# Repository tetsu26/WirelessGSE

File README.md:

# GSE Ver.2 の解説
東北大学FROM THE EARTH用のGSE制御システムVer.2の解説です．    
質問等は tetsushi_m[at]outlook.jp まで．

# はじめに
FTEのGSEを無線化した経緯について書いておきます．

時は遡ること2017年，この年の能代で突然，点火点と射点の位置が20mくらい伸びたため，今まで使っていたGSEのケーブルの長さが足りなくなってしまったのです．そこで燃焼班の皆様はLANケーブルを調達し，なんか頑張ってどうにかなった（詳しくはよく知らん）のですが，そのときの燃焼班のケーブル半田付けなどがまぁそれはそれは残念だったので，電子班でどうにかしようということになりました．んで，当時流行だった無線GSEに憧れた7期はどうせならFTEのGSEも無線化しちまおうとなったわけです．自然な流れですね．そして当時電子班班長だった私は電子班の誰かに無線GSE開発を押しつけようと声をかけ続けた訳ですが，何かと理由をつけて全員に断られてしまったので仕方なく自分でやることにしたわけです．

そうして無線GSEを作ることになってしまった私ですが，当初はロケットの電装に比べれば，スイッチの状態を送信するだけなんで簡単だろうと高をくくっていた訳です．まぁ"スイッチの状態を送るだけなら"実際簡単な訳ですが．実際作ってみるといろいろな障壁がありました．
* 送信レートの問題
  
  IM920で使ってる920MHz帯は送信時間の制限が厳しくて，データを連続送信できないため，5Hz位でしかスイッチの状態を反映できない．
* IM920 の通信距離
  
  7km飛ぶとかいっときながら見通しでも300m位しか通信できない．ちょっと怖い．
* 打ち上げシーケンス中に通信途切れた時の対処
  
  ダンプするしかない．悲しい．
* 卍伊豆大島卍
  
  活火山なだけあって何かが島から出ている．無線が飛ばない．見通しで100mがやっと．
* 責任
  
  無線GSEがしくじるとロケットが飛ばない訳でみんなの努力が報われない．打ち上げ前は気が気じゃない．
  
そのたもろもろ．思ったより大変だった．

そんなこんなで無線GSEを作っていると思うわけです．点火点と射点，ケーブルでつなげばよくね？　俗に言う原点回帰って奴です．有線なら通信の安定性とか考えなくていいし，ケーブルの断線だけ気をつけていればいいよね．そこで電子班何人かで有線GSEを総点検し，やばそうな半田付けは直し，ケーブルも完璧に作り直しました．

つまり，このくそ長いはじめにで何が言いたいかというと，**「無線使うな有線を使え」** ということです．きっとこれを読んでいるあなたは不幸にも無線GSEを押しつけられてしまったしがない電子班員でしょう．ご愁傷さま．燃焼班員にあったら是非伝えてください． **「無線使うな有線を使え」** と．あいつらはこの無線GSEのやばさを知りません．健闘を祈ります．

# よく燃焼班に聞かれること・注意すべきこと
* 無線のチャンネルは？  
  プログラムコードからは変更できない．IM920の設定から変更する．ググれば出てくるし，[この辺のサイト](https://www.interplan.co.jp/solution/wireless/im920/im920.php)を参考にすべし．

* 安全対策は？  
  万が一Fill中に通信が途絶えてもFillが止まるように，Fillには時間制限がかかっている．時間制限はロケット側のGSEのプログラムを書き換えることで変更できる．デフォルトでは60秒以上Fillが続くと強制的に30秒ダンプする．  
  同様に，Oxyも60秒以上入らないようになっている．このときはダンプせず，システムを再起動する．

# 使っている主な部品  
* マイコン    MBED LPC1768  
まぁいつもの．ピンがいっぱいあるから．
* 3端子dcdc   BP5293-50   http://akizukidenshi.com/catalog/g/gM-11188/  
3端子レギュレーターは効率悪いし，村田のdcdcコンバータは半田付けが難しすぎるので．  
ざっと計算した感じ，1Aもあれば，IM920含めて余裕で足りる．
* リレー    946H-1C-5D  http://akizukidenshi.com/catalog/g/gP-07342/  
mbedのdigital out は40mAまでしか出せないので，リレーは動かせなさそうだった．  
5Vのリレーをトランジスタでスイッチングするのがいいと思った．   
* 無線モジュール    IM920  
協賛でもらったやつ．正直無線GSEには向いてない．

# プログラムコード
\SourceCode にあります．mbedオンラインコンパイラにコピペして使ってください．
ロケット側と点火点側でソースコードが分かれてるんで気をつけてください．

## コード解説_点火点側
ソースコードはc++(ほぼC)で書いてあります．一応頭から説明しておきます．

```cpp
#include<mbed.h>
#include<IM920.h>
#include<cstring>
```
ライブラリのインポートです（それはそう）．

```cpp
#define IM920_TX p13
#define IM920_RX p14
#define IM920_BUSY p11
#define IM920_RESET p12
#define IM920_SERIAL_BANDRATE 19200//im920の通信レート
```
IM920関係のピン設定ですね．

```cpp
DigitalOut myled(LED1);
DigitalOut myled2(LED2);
DigitalOut myled3(LED3);
DigitalOut myled4(LED4);
DigitalOut led_fill(p16);
DigitalOut led_dump(p18);
DigitalOut led_oxy(p20);
DigitalOut led_fire(p21);
DigitalOut led_1(p24);
DigitalOut led_2(p23);
PwmOut buzzer(p26);

DigitalIn fill(p15);
DigitalIn dump(p17);
DigitalIn oxy(p19);
DigitalIn fire(p22);

IM920 im920(p13, p14, p11, p12,19200);//無線通信用のserialクラス
Serial pc(USBTX, USBRX);
```
そのたもろもろのピン設定です．基板自作したときは適宜変えてください．

```cpp
// グローバルな奴ら
char send_data[8];    //送信するデータを格納する変数
char recv_data[8];    //受信すry)
int cb_count = 0;     //割り込み回数を数えるやつ
int i = 0;            //一秒間隔で赤いLEDを点滅させるのに使う
```
グローバル変数です．

```cpp
int fire_buzzer(int i)
{
    if(i == 1)
    {
        buzzer.period(1.0/440.0);  //多分"ラ"
        buzzer.write(0.5f);
        wait(0.5f);
        buzzer.write(0.0f);
    }
    
    return 0;
}
```
これは fire をオンにしたときにブザーから音を出すための関数です．音程が気に入らない人は変えてください．

### callback() 関数

```cpp
void callback () {  //受信時の割り込み関数（受信したときに送信するコード）
    int i;

    cb_count++; //割り込みの回数を数える変数
    
    i = im920.recv(recv_data, 8);
    recv_data[i] = 0;
    pc.printf("recv: '%s' (%d)\r\n", recv_data, i);
    
    if (recv_data[0] == '5' || recv_data[7] == '5')     //きちんとデータを受け取れたか確認
    {
        led_fill = recv_data[1] - '0';           
        led_dump = recv_data[2] - '0';
        led_oxy = recv_data[3] - '0';
        led_fire = recv_data[4] - '0';
        fire_buzzer(led_fire);
    }
    //8文字1セットで送ることにする
    send_data[0] = '5';   //データ始まりの合図
    send_data[1] = '0'+(fill.read()^ 1);      //プルアップしてるからHiとLoを反転
    send_data[2] = '0'+(dump.read()^ 1);
    send_data[3] = '0'+(oxy.read()^ 1);
    send_data[4] = '0'+(fire.read()^ 1);
    // 5~6はとりあえず未使用
    send_data[5] = '0';
    send_data[6] = '0';
    send_data[7] = '5';   //データ終わりの合図
        
    im920.sendData(send_data,8);    //8文字送りますよーってやつ
    //pc.printf("send:%s\r\n cb_count:%d\r\n",send_data,cb_count);

}
```
これはim920が受信したときに実行される予定の関数です．グローバル関数にiがあるのにローカルでもiを宣言して使うくそコードになってますね，今気づきました．ここからわかりにくいと思うので詳しく書いておきます．
```cpp
i = im920.recv(recv_data, 8);
recv_data[i] = 0;
pc.printf("recv: '%s' (%d)\r\n", recv_data, i);
```
この辺はおまじないです．書いておいてください．
```cpp
if (recv_data[0] == '5' || recv_data[7] == '5')     //きちんとデータを受け取れたか確認
    {
        led_fill = recv_data[1] - '0';           
        led_dump = recv_data[2] - '0';
        led_oxy = recv_data[3] - '0';
        led_fire = recv_data[4] - '0';
        fire_buzzer(led_fire);
    }
```
これは効果あるかは謎ですが，受信したデータの整合性を確認しているつもりです．受信データ（8桁）の最初と最後の数字は`5`なのでそれだけ確認しています．

その後の`led_fill = recv_data[1] - '0';`ですが，これは受信した8桁の2文字目がfillの状態を示しているのでそれをスイッチについたLEDに反映しています．受信したデータは`recv_data`に格納されているのですが，ASCIIコードなので`0`のASCIIコードを引くことで元の送信した数字に戻しています．ほかも同じです．
```cpp
 //8文字1セットで送ることにする
    send_data[0] = '5';   //データ始まりの合図
    send_data[1] = '0'+(fill.read()^ 1);      //プルアップしてるからHiとLoを反転
    send_data[2] = '0'+(dump.read()^ 1);
    send_data[3] = '0'+(oxy.read()^ 1);
    send_data[4] = '0'+(fire.read()^ 1);
    // 5~6はとりあえず未使用
    send_data[5] = '0';
    send_data[6] = '0';
    send_data[7] = '5';   //データ終わりの合図
```
この辺はスイッチの状態を読み取って送信するデータを作っています．`send_data`配列の５と６は将来のために未使用です．送る文字数を８文字にしたのはなんとなくきりがいいからです．
```cpp
im920.sendData(send_data,8);    //8文字送りますよーってやつ
```
そしてここで上で作った文字列を送信しています．

### callback2() 関数
```cpp
void callback2()    //受信割り込みの回数を数える関数
{
    
    if(cb_count == 0)
    {
        pc.printf("yabame\r\n");
        NVIC_SystemReset();         //一秒間に一回も通信しなかったらリセットする
        
    }
    else
    {
        cb_count = 0;
        if(i == 0)
        {
            led_2 = 1;
            i++;
        }else{
            led_2 = 0;
            i = 0;
        }

    }
}
```
これは接続が切れたときの対処です．コードをざっくり見てもらうと気づくと思うのですが，このコードには「受信したら割り込み処理で送信する」機能しかないので，一度接続が切れる（というかデータのやりとりが途絶える）と復帰できなくなる問題があります．なので`callback2()`関数を1秒ごとに起動してもしその前1秒間に一度も通信していなかったらこのmbedをリセットして`main()`関数をもう一度頭から実行します．`NVIC_SystemReset()`ってのはmbedのリセットボタンを押した状態をコードから作れる魔法の言葉です．

### main()関数
```cpp
int main()
{
    //各スイッチをプルアップする
    fill.mode(PullUp);
    dump.mode(PullUp);
    oxy.mode(PullUp);
    fire.mode(PullUp);          

    im920.init();
    //Im920受信の割り込みを設定
    im920.attach(callback);
    pc.baud(115200);
    pc.printf("Wireless GSE controll system started!!\r\n");
    
    Ticker timeout;
    timeout.attach(&callback2,1);
    
    myled = 1;  //設定完了の合図
    led_1 = 1; 
    im920.poll();
    im920.sendData(send_data,8);    
    
    while(1){   
        im920.poll();//双方向送受信に必要らしい
       // wait_ms(1);  //意味なさそうだけどあると安定する
        
    }
    
}
```
ここは特に説明することもない気がします．セットアップの時に1度データを送信します．

## コード解説_ロケット側
同じように解説書いておきます．
```cpp
#include<mbed.h>
#include<IM920.h>

#define IM920_TX p13
#define IM920_RX p14
#define IM920_BUSY p11
#define IM920_RESET p12
#define IM920_SERIAL_BANDRATE 19200//im920の通信レート

//LED&SWITCHたち      
DigitalOut myled(LED1);
DigitalOut myled2(LED2);
DigitalOut myled3(LED3);
DigitalOut myled4(LED4);
DigitalOut fill(p21);
DigitalOut dump(p22);
DigitalOut oxy(p23);
DigitalOut fire(p24);

IM920 im920(p13, p14, p11, p12,19200);//無線通信用のserialクラス
Serial pc(USBTX, USBRX);
```
まぁこの辺は説明するまでもないでしょ．
```cpp
char send_data[8];    //送信するデータを格納する変数
char recv_data[8];    //受信すry)
int fill_count = 0;     //fillの割り込みの回数を数えるやつ
int oxy_count = 0;     //oxyの割り込みの回数を数えるやつ
```
グローバル変数の定義．

### callback()関数
```cpp
void callback () {
    int i;
    int fire_count = 0;
    
    i = im920.recv(recv_data, 8);
    recv_data[i] = 0;
    printf("recv: '%s' (%d)\r\n", recv_data, i);
    
    if (recv_data[0] == '5' || recv_data[7] == '5')     //きちんとデータを受け取れたか確認
    {
        fill = recv_data[1] - '0';           
        dump = recv_data[2] - '0';
        oxy = recv_data[3] - '0';
        fire_count = recv_data[4] - '0';
        
        if(fire_count == 1 && oxy == 1){
            fire = 1;
        }else{
            fire = 0;
        }
        
    }
    /*
    for(int i = 0; i < 8; i++)
    {
        send_data[i] = recv_data[i];
    }
    */
    im920.sendData(recv_data,8);
    //printf("send!!:%s\r\n",recv_data);
}
```
点火点側の`callback`関数とほとんど同じです．ただ，`oxy`が入ってないと`fire`がオンにならないようにしてあります．

### fillcount()関数
```cpp
void fillcount()    //受信割り込みの回数を数える関数
{
    if(fill == 1)
    {
        fill_count += 1;
    }else{
        fill_count = 0;
    }
    
    if(oxy == 1)
    {
        oxy_count += 1;
    }else{
        oxy_count = 0;
    }
    
    printf("fill_count: %d\r\n",fill_count);
    printf("oxy_count: %d\r\n",oxy_count);
    if(fill_count >= 60)
    {
        fill = 0;
        dump = 1;
        printf("recovery mode!!! Dump 30second\r\n");
        wait(30);
        printf("reboot!!");
        NVIC_SystemReset(); 
        
    }
    if(oxy_count >= 60)
    {
        oxy = 0;
        printf("recovery mode!!!\r\n");
        printf("reboot!!");
        NVIC_SystemReset(); 
    }
    
}
```
この関数を1秒に一回割り込みさせることで，`fill`がオンになってる秒数などを数えています．
```cpp 
if(fill_count >= 60)
```
の60をいじるとFill時間に制限をかけられます．60の時は一分以上はFillできないという具合です．

### main()関数
```cpp
int main()
{
    
    pc.baud(115200);
    pc.printf("*** IM920\r\n");
    
    /* 受信側との接続を確立する */
    
    im920.init();

    im920.attach(callback);
    myled = 1;          //設定完了の合図
    
    Ticker fill_limit;
    fill_limit.attach(&fillcount,1);
    
    im920.poll();

    while(1){
       im920.poll();
       //wait_ms(1);
    }
    
}
```
特にいうことはないです．
```cpp
    Ticker fill_limit;
    fill_limit.attach(&fillcount,1);
```
でfillcount関数に1秒おきの割り込みを設定しています．

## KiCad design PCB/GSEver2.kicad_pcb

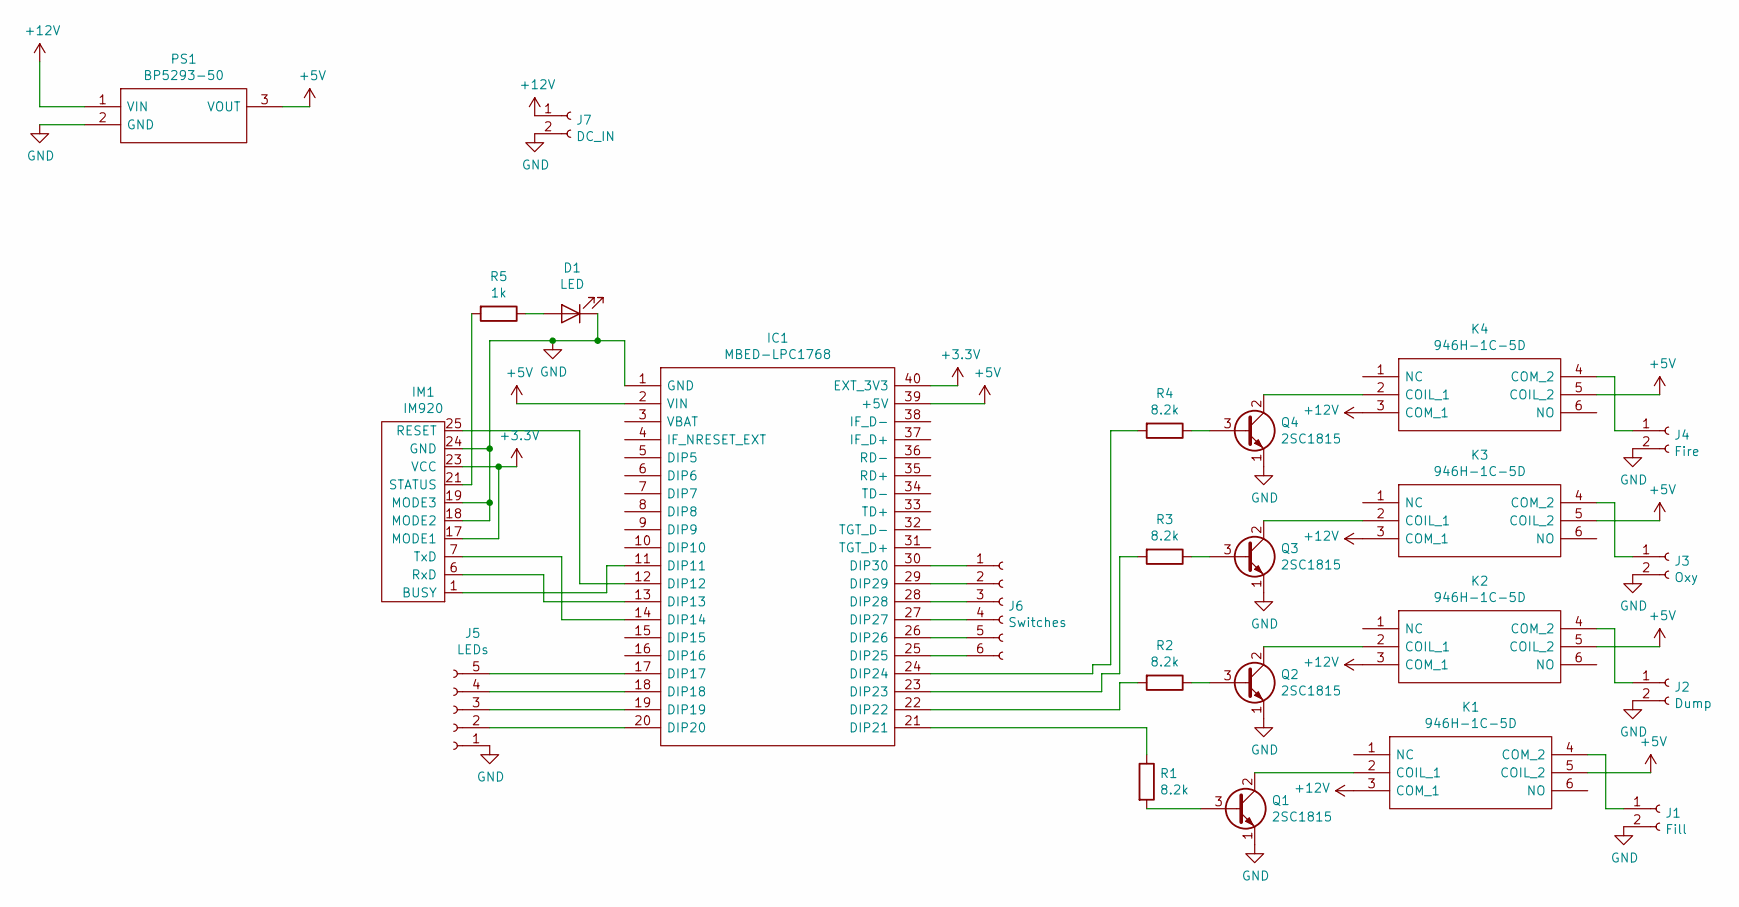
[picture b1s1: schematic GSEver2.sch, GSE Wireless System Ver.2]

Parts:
D1: LED; LED_D3.0mm
IC1: MBED-LPC1768; DIPS2286W63P254L5370H300Q40N; Manufacturer_Part_Number MBED-LPC1768
IM1: IM920
J1: Fill; JST_XH_B02B-XH-A_02x2.50mm_Straight
J2: Dump; JST_XH_B02B-XH-A_02x2.50mm_Straight
J3: Oxy; JST_XH_B02B-XH-A_02x2.50mm_Straight
J4: Fire; JST_XH_B02B-XH-A_02x2.50mm_Straight
J5: LEDs; JST_XH_B05B-XH-A_05x2.50mm_Straight
J6: Switches; JST_XH_B06B-XH-A_06x2.50mm_Straight
J7: DC_IN; JST_XH_B02B-XH-A_02x2.50mm_Straight
K1, K2, K3, K4: 946H-1C-5D; 946H1C5D; Manufacturer_Part_Number 946H-1C-5D
PS1: BP5293-50; TO254P570X1690X1800-3P; Manufacturer_Part_Number BP5293-50
Q1, Q2, Q3, Q4: 2SC1815; TO-92_Inline
R1, R2, R3, R4: 8.2k; R_Axial_DIN0207_L6.3mm_D2.5mm_P10.16mm_Horizontal
R5: 1k; R_Axial_DIN0207_L6.3mm_D2.5mm_P10.16mm_Horizontal

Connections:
+3V3: IC1.40 (EXT_3V3), IM1.17 (MODE1), IM1.23 (VCC); also elsewhere on the board
+5V: IC1.2 (VIN), IC1.39 (+5V), K1.5 (COIL_2), K2.5 (COIL_2), K3.5 (COIL_2), K4.5 (COIL_2), PS1.3 (VOUT); also elsewhere on the board
+12V: J7.1, K1.3 (COM_1), K2.3 (COM_1), K3.3 (COM_1), K4.3 (COM_1), PS1.1 (VIN)
GND: D1.1 (K), IC1.1 (GND), IM1.18 (MODE2), IM1.19 (MODE3), IM1.24 (GND), J1.2, J2.2, J3.2, J4.2, J5.1, J7.2, PS1.2 (GND), Q1.1 (E), Q2.1 (E), Q3.1 (E), Q4.1 (E); also elsewhere on the board
unnamed: D1.2 (A), R5.1
unnamed 13: IC1.11 (DIP11), IM1.1 (BUSY); also elsewhere on the board
unnamed 14: IC1.12 (DIP12), IM1.25 (RESET); also elsewhere on the board
unnamed 15: IC1.13 (DIP13), IM1.6 (RxD); also elsewhere on the board
unnamed 16: IC1.14 (DIP14), IM1.7 (TxD); also elsewhere on the board
unnamed 19: IC1.17 (DIP17), J5.5; also elsewhere on the board
unnamed 20: IC1.18 (DIP18), J5.4; also elsewhere on the board
unnamed 21: IC1.19 (DIP19), J5.3; also elsewhere on the board
unnamed 22: IC1.20 (DIP20), J5.2; also elsewhere on the board
unnamed 23: IC1.21 (DIP21), R1.1; also elsewhere on the board
unnamed 24: IC1.22 (DIP22), R2.2; also elsewhere on the board
unnamed 25: IC1.23 (DIP23), R3.2; also elsewhere on the board
unnamed 26: IC1.24 (DIP24), R4.2; also elsewhere on the board
unnamed 27: IC1.25 (DIP25), J6.6; also elsewhere on the board
unnamed 28: IC1.26 (DIP26), J6.5; also elsewhere on the board
unnamed 29: IC1.27 (DIP27), J6.4; also elsewhere on the board
unnamed 30: IC1.28 (DIP28), J6.3; also elsewhere on the board
unnamed 31: IC1.29 (DIP29), J6.2; also elsewhere on the board
unnamed 32: IC1.30 (DIP30), J6.1; also elsewhere on the board
unnamed: IM1.21 (STATUS), R5.2
unnamed: J1.1, K1.4 (COM_2)
unnamed: J2.1, K2.4 (COM_2)
unnamed: J3.1, K3.4 (COM_2)
unnamed: J4.1, K4.4 (COM_2)
unnamed: K1.2 (COIL_1), Q1.2 (C)
unnamed: K2.2 (COIL_1), Q2.2 (C)
unnamed: K3.2 (COIL_1), Q3.2 (C)
unnamed: K4.2 (COIL_1), Q4.2 (C)
unnamed: Q1.3 (B), R1.2
unnamed: Q2.3 (B), R2.1
unnamed: Q3.3 (B), R3.1
unnamed: Q4.3 (B), R4.1

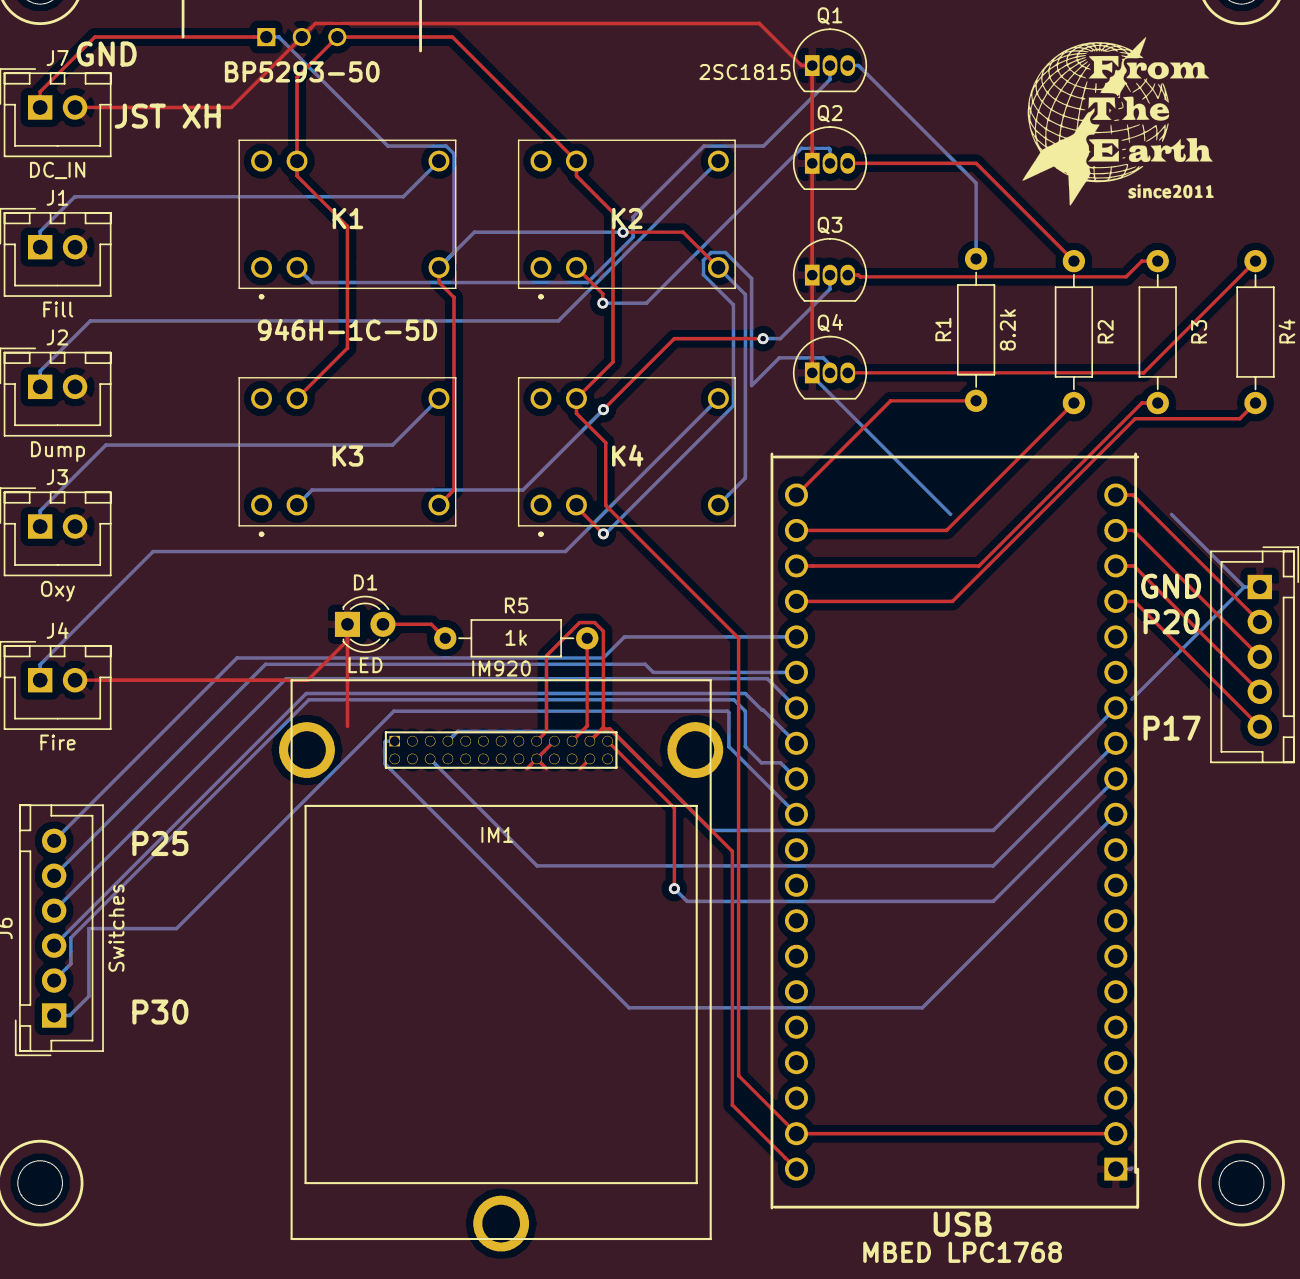
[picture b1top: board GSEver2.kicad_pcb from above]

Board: 2 copper layers, 25 parts (0 on the bottom side), 36 nets.

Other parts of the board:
LEDs: LEDs; JST_XH_B05B-XH-A_05x2.50mm_Straight
M3: MountingHole_3.2mm_M3_ISO14580
MBED LPC1768: MBED-LPC1768; DIPS2286W63P254L5370H300Q40N

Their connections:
+3V3: MBED LPC1768.40; also elsewhere on the board
+5V: MBED LPC1768.2, MBED LPC1768.39; also elsewhere on the board
GND: LEDs.1, MBED LPC1768.1; also elsewhere on the board
unnamed 13: MBED LPC1768.11; also elsewhere on the board
unnamed 14: MBED LPC1768.12; also elsewhere on the board
unnamed 15: MBED LPC1768.13; also elsewhere on the board
unnamed 16: MBED LPC1768.14; also elsewhere on the board
unnamed 19: LEDs.5, MBED LPC1768.17; also elsewhere on the board
unnamed 20: LEDs.4, MBED LPC1768.18; also elsewhere on the board
unnamed 21: LEDs.3, MBED LPC1768.19; also elsewhere on the board
unnamed 22: LEDs.2, MBED LPC1768.20; also elsewhere on the board
unnamed 23: MBED LPC1768.21; also elsewhere on the board
unnamed 24: MBED LPC1768.22; also elsewhere on the board
unnamed 25: MBED LPC1768.23; also elsewhere on the board
unnamed 26: MBED LPC1768.24; also elsewhere on the board
unnamed 27: MBED LPC1768.25; also elsewhere on the board
unnamed 28: MBED LPC1768.26; also elsewhere on the board
unnamed 29: MBED LPC1768.27; also elsewhere on the board
unnamed 30: MBED LPC1768.28; also elsewhere on the board
unnamed 31: MBED LPC1768.29; also elsewhere on the board
unnamed 32: MBED LPC1768.30; also elsewhere on the board

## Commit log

2019-06-18 Delete Specification.md
    このファイルいらなくね？
2019-07-03 ソースコードぶち上げた
2019-07-03 Set theme jekyll-theme-cayman
2019-07-03 Update README.md
    色つけた
2019-07-18 書き足した
2019-07-23 はじめにを書いた
2019-07-25 ロケット側のコード解説も書いた

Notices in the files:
PCB/GSEver2.kicad_pcb:
©Tetsushi Amano, 2019
